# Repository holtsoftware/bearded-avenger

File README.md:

bearded-avenger
===============

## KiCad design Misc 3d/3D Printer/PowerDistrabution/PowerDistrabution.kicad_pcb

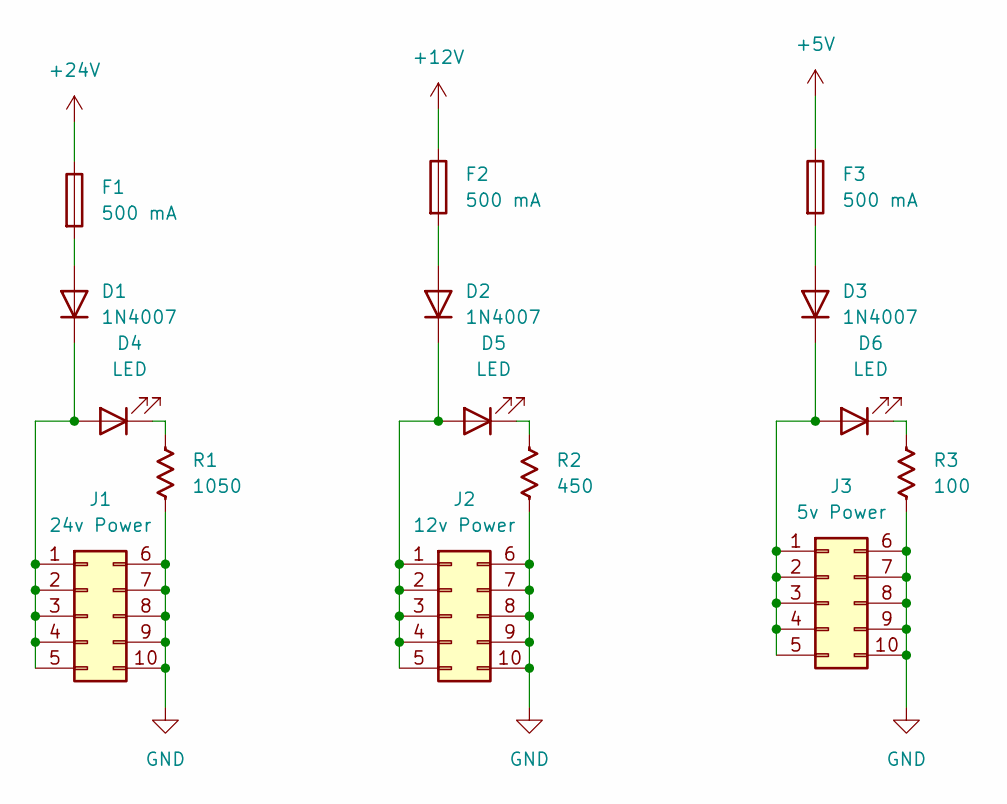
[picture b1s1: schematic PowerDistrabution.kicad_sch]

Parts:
D1, D2, D3: 1N4007; D_DO-41_SOD81_P10.16mm_Horizontal
D4, D5, D6: LED; LED_D5.0mm
F1, F2, F3: 500 mA; R_Axial_DIN0207_L6.3mm_D2.5mm_P15.24mm_Horizontal
J1: 24v Power; PinHeader_2x05_P1.00mm_Vertical
J2: 12v Power; PinHeader_2x05_P1.00mm_Vertical
J3: 5v Power; PinHeader_2x05_P1.00mm_Vertical
R1: 1050; R_Axial_DIN0207_L6.3mm_D2.5mm_P10.16mm_Horizontal
R2: 450; R_Axial_DIN0207_L6.3mm_D2.5mm_P10.16mm_Horizontal
R3: 100; R_Axial_DIN0207_L6.3mm_D2.5mm_P10.16mm_Horizontal

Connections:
+5V: F3.1
+12V: F2.1
+24V: F1.1
GND: J1.6, J1.7, J1.8, J1.9, J1.10, J2.6, J2.7, J2.8, J2.9, J2.10, J3.6, J3.7, J3.8, J3.9, J3.10, R1.2, R2.2, R3.2
unnamed: D1.2 (A), F1.2
unnamed: D1.1 (K), D4.2 (A), J1.1, J1.2, J1.3, J1.4, J1.5
unnamed: D2.2 (A), F2.2
unnamed: D2.1 (K), D5.2 (A), J2.1, J2.2, J2.3, J2.4, J2.5
unnamed: D3.2 (A), F3.2
unnamed: D3.1 (K), D6.2 (A), J3.1, J3.2, J3.3, J3.4, J3.5
unnamed: D4.1 (K), R1.1
unnamed: D5.1 (K), R2.1
unnamed: D6.1 (K), R3.1

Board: 2 copper layers, 15 parts (0 on the bottom side), 10 nets, no tracks yet.

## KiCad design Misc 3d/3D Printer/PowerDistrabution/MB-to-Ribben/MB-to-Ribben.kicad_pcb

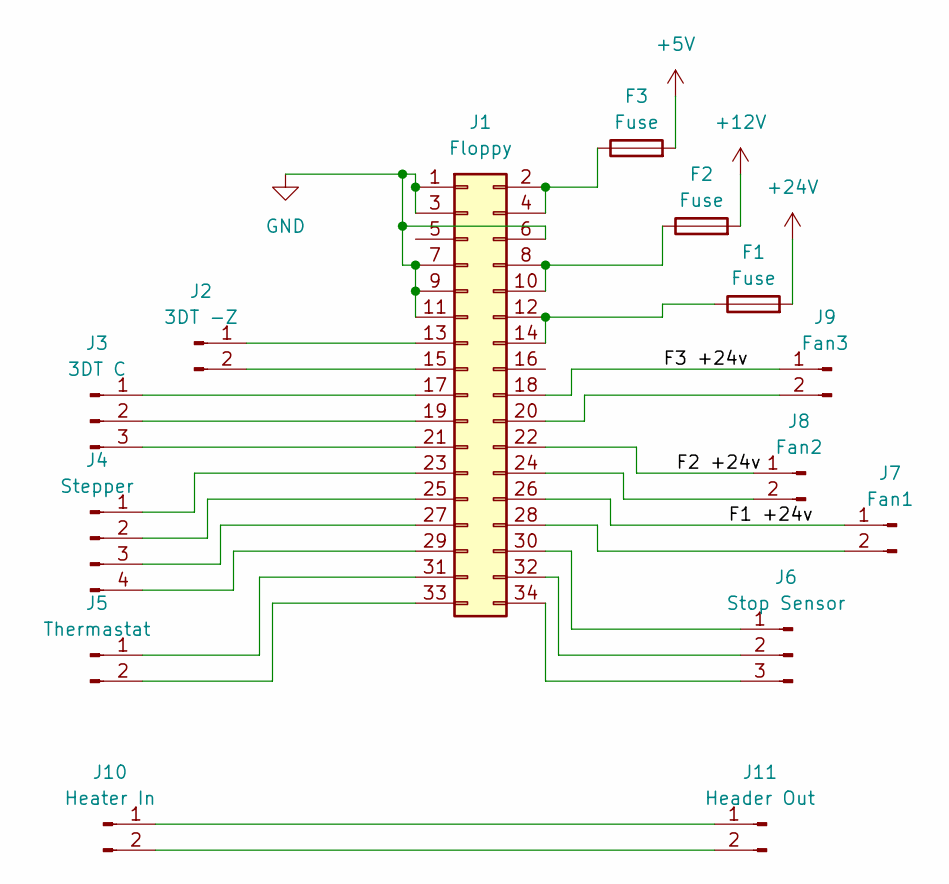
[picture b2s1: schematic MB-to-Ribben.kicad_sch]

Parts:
F1, F2, F3: Fuse; TerminalBlock_bornier-2_P5.08mm
J1: Floppy; PinHeader_2x17_P2.54mm_Vertical
J2: 3DT -Z; JST_XH_B2B-XH-A_1x02_P2.50mm_Vertical
J3: 3DT C; JST_XH_B3B-XH-A_1x03_P2.50mm_Vertical
J4: Stepper; JST_XH_B4B-XH-A_1x04_P2.50mm_Vertical
J5: Thermastat; JST_XH_B2B-XH-A_1x02_P2.50mm_Vertical
J6: Stop Sensor; JST_XH_B3B-XH-A_1x03_P2.50mm_Vertical
J7: Fan1; JST_XH_B2B-XH-A_1x02_P2.50mm_Vertical
J8: Fan2; JST_XH_B2B-XH-A_1x02_P2.50mm_Vertical
J9: Fan3; JST_XH_B2B-XH-A_1x02_P2.50mm_Vertical
J10: Heater In; TerminalBlock_bornier-2_P5.08mm
J11: Header Out; TerminalBlock_bornier-2_P5.08mm

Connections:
+5V: F3.2
+12V: F2.2
+24V: F1.2
/F1 +24v: J1.26, J7.1
/F2 +24v: J1.22, J8.1
/F3 +24v: J1.18, J9.1
GND: J1.1, J1.3, J1.6, J1.7, J1.9, J1.11
unnamed: F3.1, J1.2, J1.4
unnamed: F2.1, J1.8, J1.10
unnamed: F1.1, J1.12, J1.14
unnamed: J1.13, J2.1
unnamed: J1.15, J2.2
unnamed: J1.17, J3.1
unnamed: J1.19, J3.2
unnamed: J1.20, J9.2
unnamed: J1.21, J3.3
unnamed: J1.23, J4.1
unnamed: J1.24, J8.2
unnamed: J1.25, J4.2
unnamed: J1.27, J4.3
unnamed: J1.28, J7.2
unnamed: J1.29, J4.4
unnamed: J1.30, J6.1
unnamed: J1.31, J5.1
unnamed: J1.32, J6.2
unnamed: J1.33, J5.2
unnamed: J1.34, J6.3
unnamed: J10.1, J11.1
unnamed: J10.2, J11.2

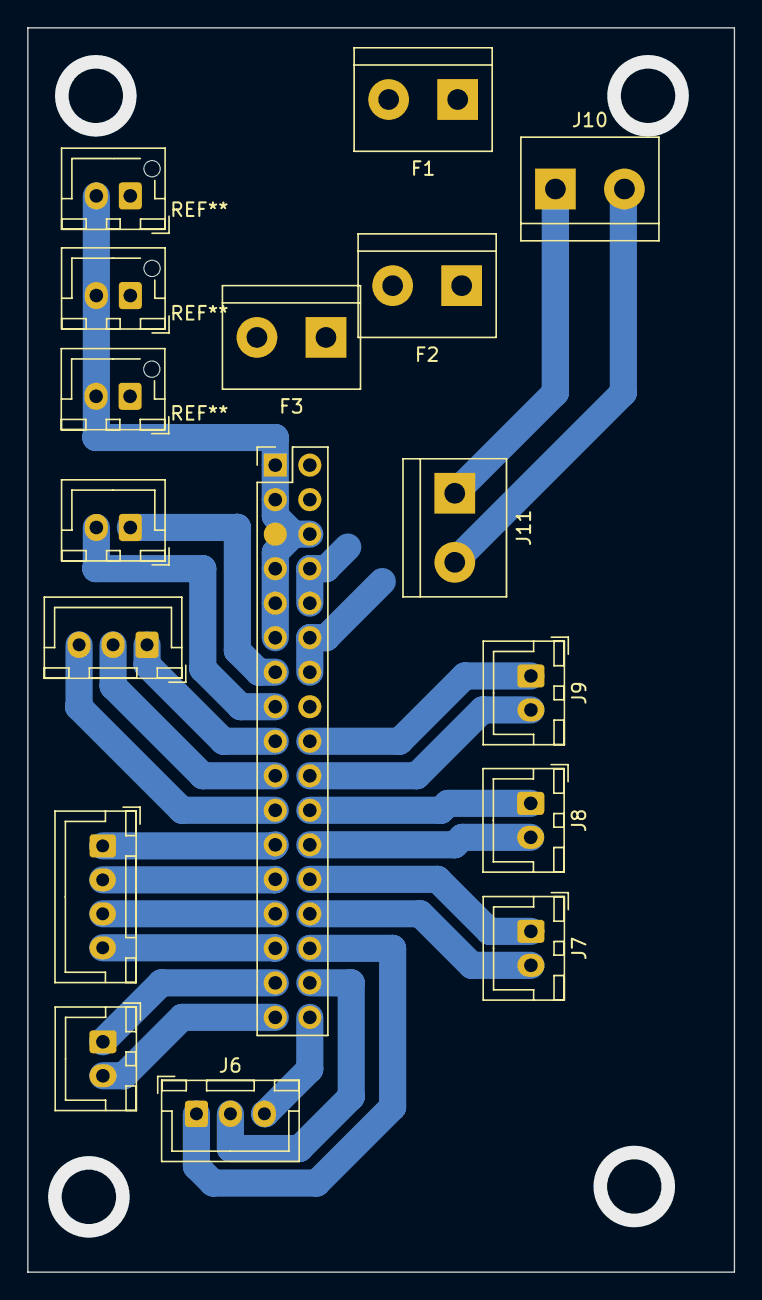
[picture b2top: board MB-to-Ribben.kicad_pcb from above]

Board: 2 copper layers, 52.0 x 91.6 mm, 14 parts (0 on the bottom side), 26 nets.

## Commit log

2014-08-08 Added Start of main Board
2014-08-12 Added Missing Files
2014-08-12 Files.
2015-02-05 A Few changes.
2015-03-03 FRMR
2015-06-28 added cupholderinsert and Rail case
2015-09-06 added more models
2015-09-20 added Code for Joey's lamp and some models
2015-09-30 Added uncommited items.
2015-10-09 Added ShutOffPower Program Code
2015-10-09 Added Files
2016-10-24 Added TalkingWall
2016-10-25 Updated credentials cache
2016-10-25 updated cert
2017-06-12 Added CurtonHook. Talkingwall ios
2017-11-16 Rebuild of Speaker Mount
2017-11-23 Added Center Mount
2017-12-30 added light supports
2018-01-11 added some more parts
2018-01-29 Progress
2018-01-30 Progress on code for WarpCore
2018-05-28 Finalized some objects.
2018-12-16 Added holder
2018-12-21 Updated WarpCore
2022-06-22 Bump Newtonsoft.Json in /TalkingWall/TalkingWall/TalkingWall.Droid
    Bumps [Newtonsoft.Json](https://github.com/JamesNK/Newtonsoft.Json) from 8.0.3 to 13.0.1.
    - [Release notes](https://github.com/JamesNK/Newtonsoft.Json/releases)
    - [Commits](https://github.com/JamesNK/Newtonsoft.Json/compare/8.0.3...13.0.1)
    ---
    updated-dependencies:
    - dependency-name: Newtonsoft.Json
2022-06-22 Bump Newtonsoft.Json in /TalkingWall/TalkingWall/TalkingWall.iOS
    Bumps [Newtonsoft.Json](https://github.com/JamesNK/Newtonsoft.Json) from 8.0.3 to 13.0.1.
    - [Release notes](https://github.com/JamesNK/Newtonsoft.Json/releases)
    - [Commits](https://github.com/JamesNK/Newtonsoft.Json/compare/8.0.3...13.0.1)
    ---
    updated-dependencies:
    - dependency-name: Newtonsoft.Json
2022-06-22 Bump Newtonsoft.Json in /TalkingWall/TalkingWall/TalkingWall.Windows
    Bumps [Newtonsoft.Json](https://github.com/JamesNK/Newtonsoft.Json) from 8.0.3 to 13.0.1.
    - [Release notes](https://github.com/JamesNK/Newtonsoft.Json/releases)
    - [Commits](https://github.com/JamesNK/Newtonsoft.Json/compare/8.0.3...13.0.1)
    ---
    updated-dependencies:
    - dependency-name: Newtonsoft.Json
2022-06-22 Bump Newtonsoft.Json in /TalkingWall/TalkingWall/TalkingWall.WinPhone
    Bumps [Newtonsoft.Json](https://github.com/JamesNK/Newtonsoft.Json) from 8.0.3 to 13.0.1.
    - [Release notes](https://github.com/JamesNK/Newtonsoft.Json/releases)
    - [Commits](https://github.com/JamesNK/Newtonsoft.Json/compare/8.0.3...13.0.1)
    ---
    updated-dependencies:
    - dependency-name: Newtonsoft.Json
2023-12-18 stuff
2024-11-24 lots of updates
